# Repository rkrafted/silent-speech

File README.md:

# silent-speech

Research notes and a first-pass hardware design for a personal **silent-speech wearable**: a device that
recognises words articulated without sound from face/jaw/neck biosignals (sEMG), in the spirit of
AlterEgo and Gaddy's silent-speech work.

> **Not tested in real life.** Nothing in this repository has been built, assembled, worn or validated on a
> real person or in a real lab. Hardware designs have only passed software checks (KiCad ERC/DRC and
> netlist scripts), and software/ML results come from offline datasets or a single dev machine. Treat
> everything as an untested design/research artefact. It is provided **as is, with no warranty**, and is
> **not a medical device** and not safe for use on people without independent engineering and safety review.

## What is here

| Path | What |
|---|---|
| `hw/` | **Current design, rev 0.7**: KiCad project for the sensor pod (nRF/NINA-B4 BLE, ADS1298 AFE), dock, cartridge and electrode/charger tabs; schematics, PCB, BOM, netlists, gerbers + pick-and-place in `hw/fab/`, `hw/SPEC.md` and `hw/pod/design-notes.md` |
| `hw/revisions/` | Earlier snapshots of the same design (schematic, PCB, BOM, notes, gerbers where they existed), named `<date>-<hash>` |
| `research/` | 12 general research tracks (SOTA, modalities, electronics, electrodes, ML pipeline, implants, DIY prior art, ear region, e-tattoos, data, Neuralink, fast personalisation) |
| `research/jaw/` | Focused sweeps: patents, PubMed, OpenBCI forum, BLE link, LCSC parts, tantalum, chip forums, articulation design |
| `scripts/`, `tools/` | Small helper scripts used by the research sweeps |
| `docs/` | Notes from one of the research tracks |

Revision snapshots:
- `hw/revisions/2026-10-07-0d3cfc9e/`
- `hw/revisions/2026-10-07-16618296/`
- `hw/revisions/2026-10-07-392cefe4/`
- `hw/revisions/2026-10-07-7efeed88/`
- `hw/revisions/2026-10-16-01f62380/`
- `hw/revisions/2026-10-16-676691bc/`
- `hw/revisions/2026-10-19-591862ab/`

## 3D models

There are **no custom 3D/CAD models** (no STEP/STL for an enclosure) in this repository: the boards reference
KiCad's stock 3D library only, and the NINA-B4 3D model referenced by the footprint was never generated.
Enclosure design has not been started.

## Notes

- Research files cite sources inline; claims marked "unverified" were not confirmed.
- Third-party datasheets, papers and scraped pages are deliberately **not** included.
- Absolute `/home/...` paths remain in some generated KiCad/router files.

## Licence

Software, scripts and documentation: MIT (`LICENSE`). Hardware design files under `hw/`:
CERN-OHL-P-2.0 (`hw/LICENSE-HARDWARE.txt`).

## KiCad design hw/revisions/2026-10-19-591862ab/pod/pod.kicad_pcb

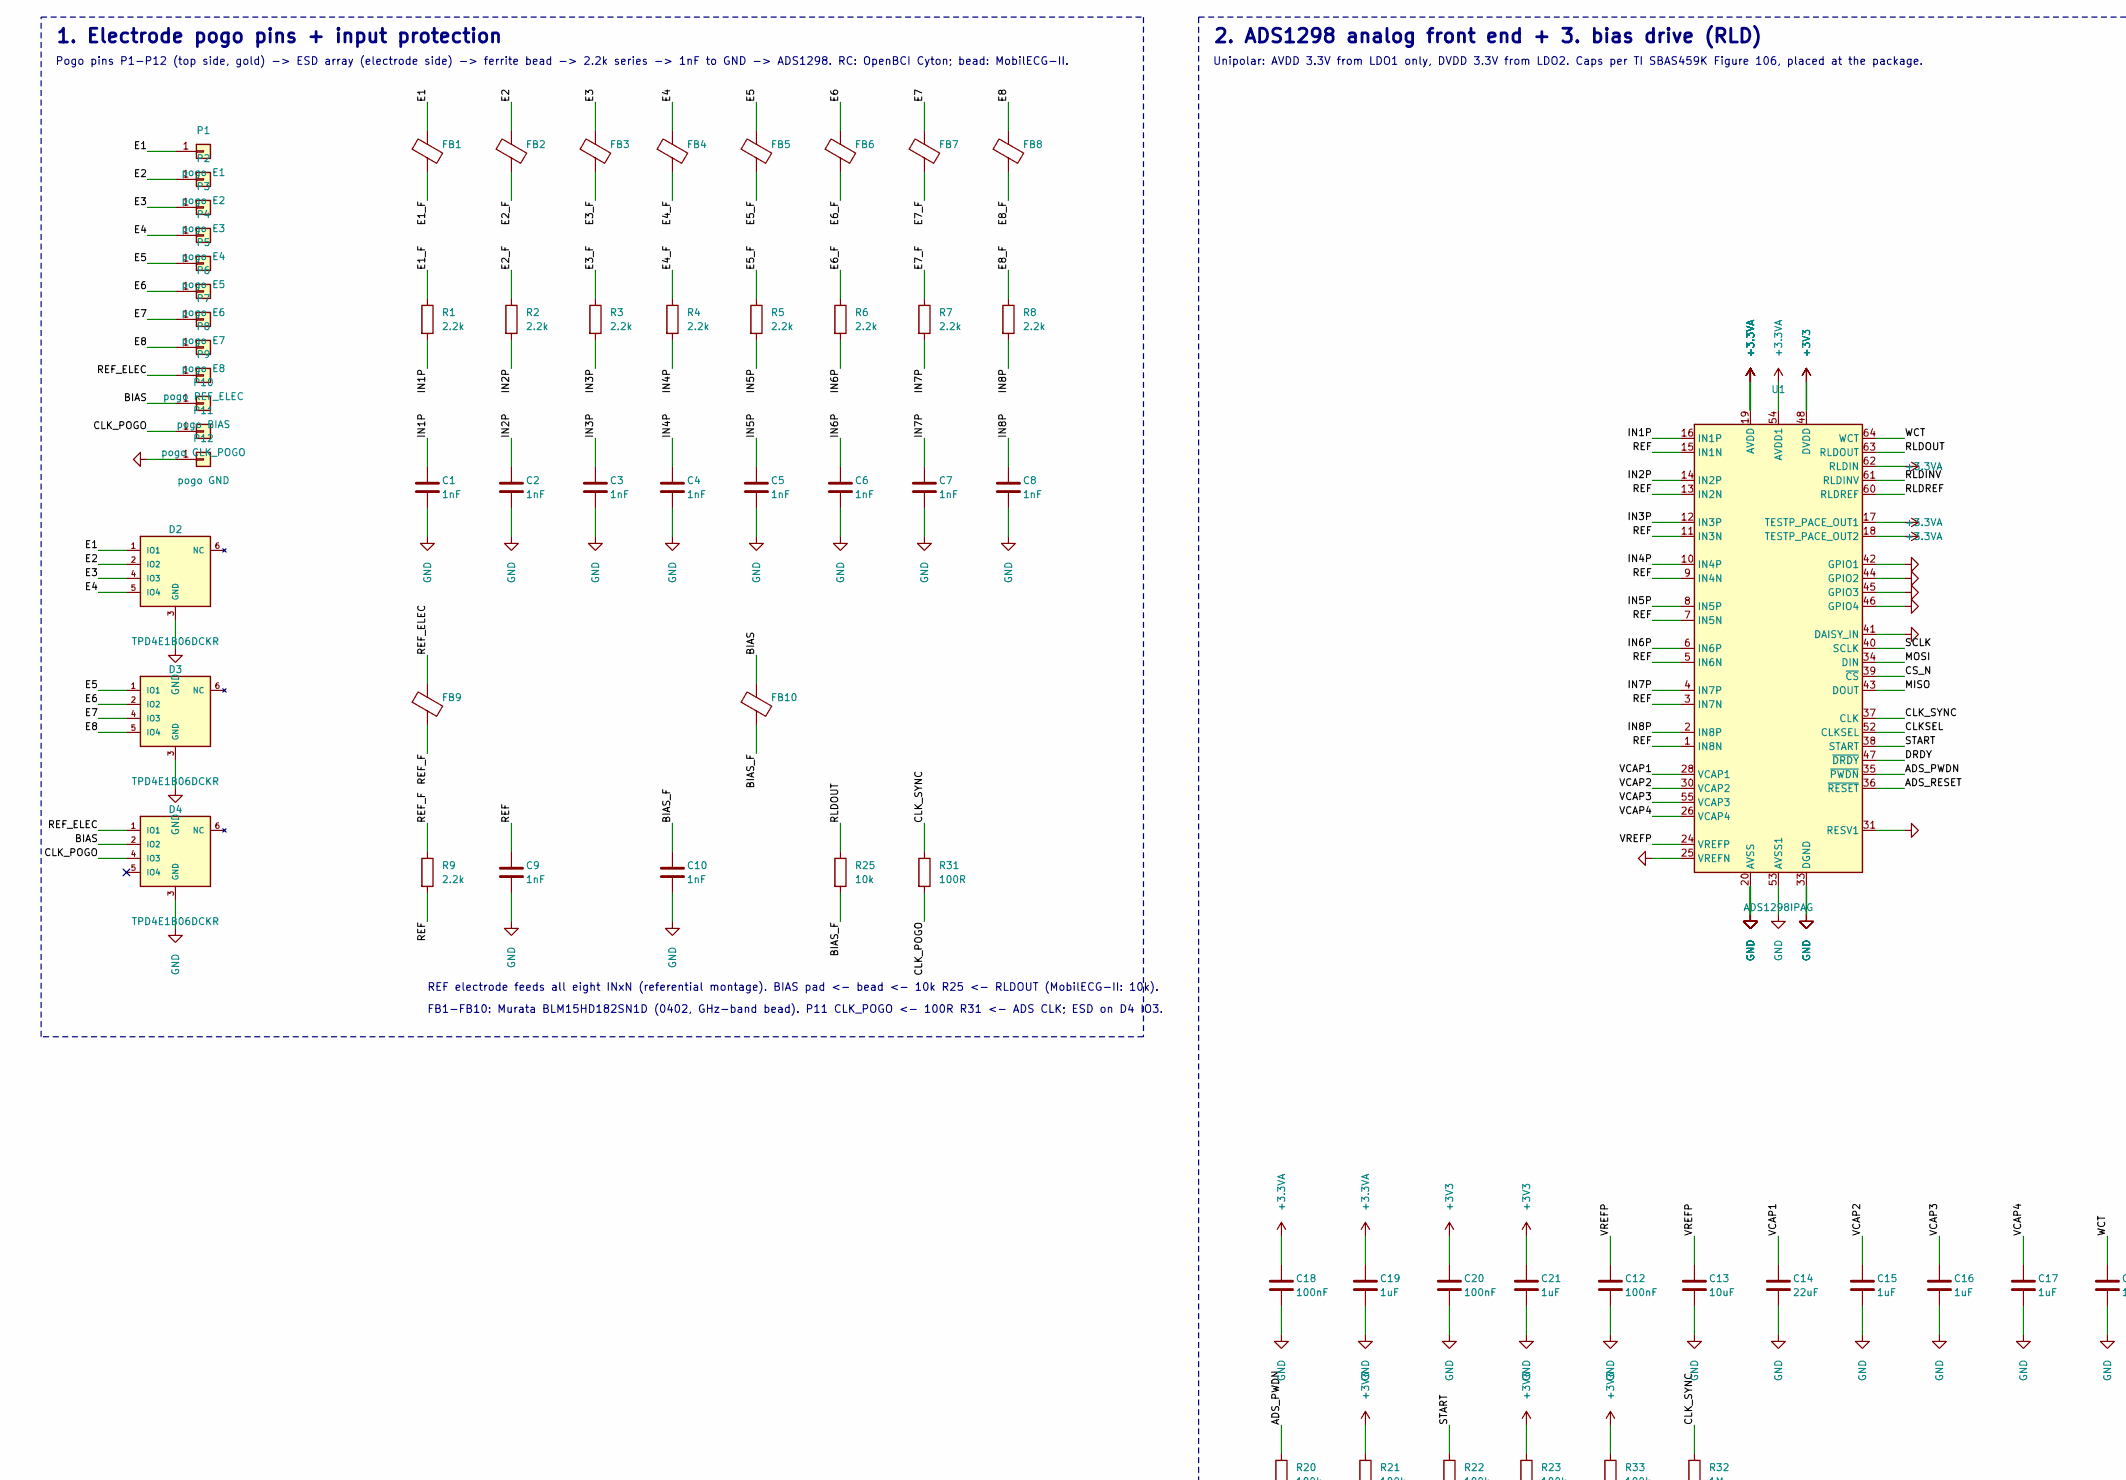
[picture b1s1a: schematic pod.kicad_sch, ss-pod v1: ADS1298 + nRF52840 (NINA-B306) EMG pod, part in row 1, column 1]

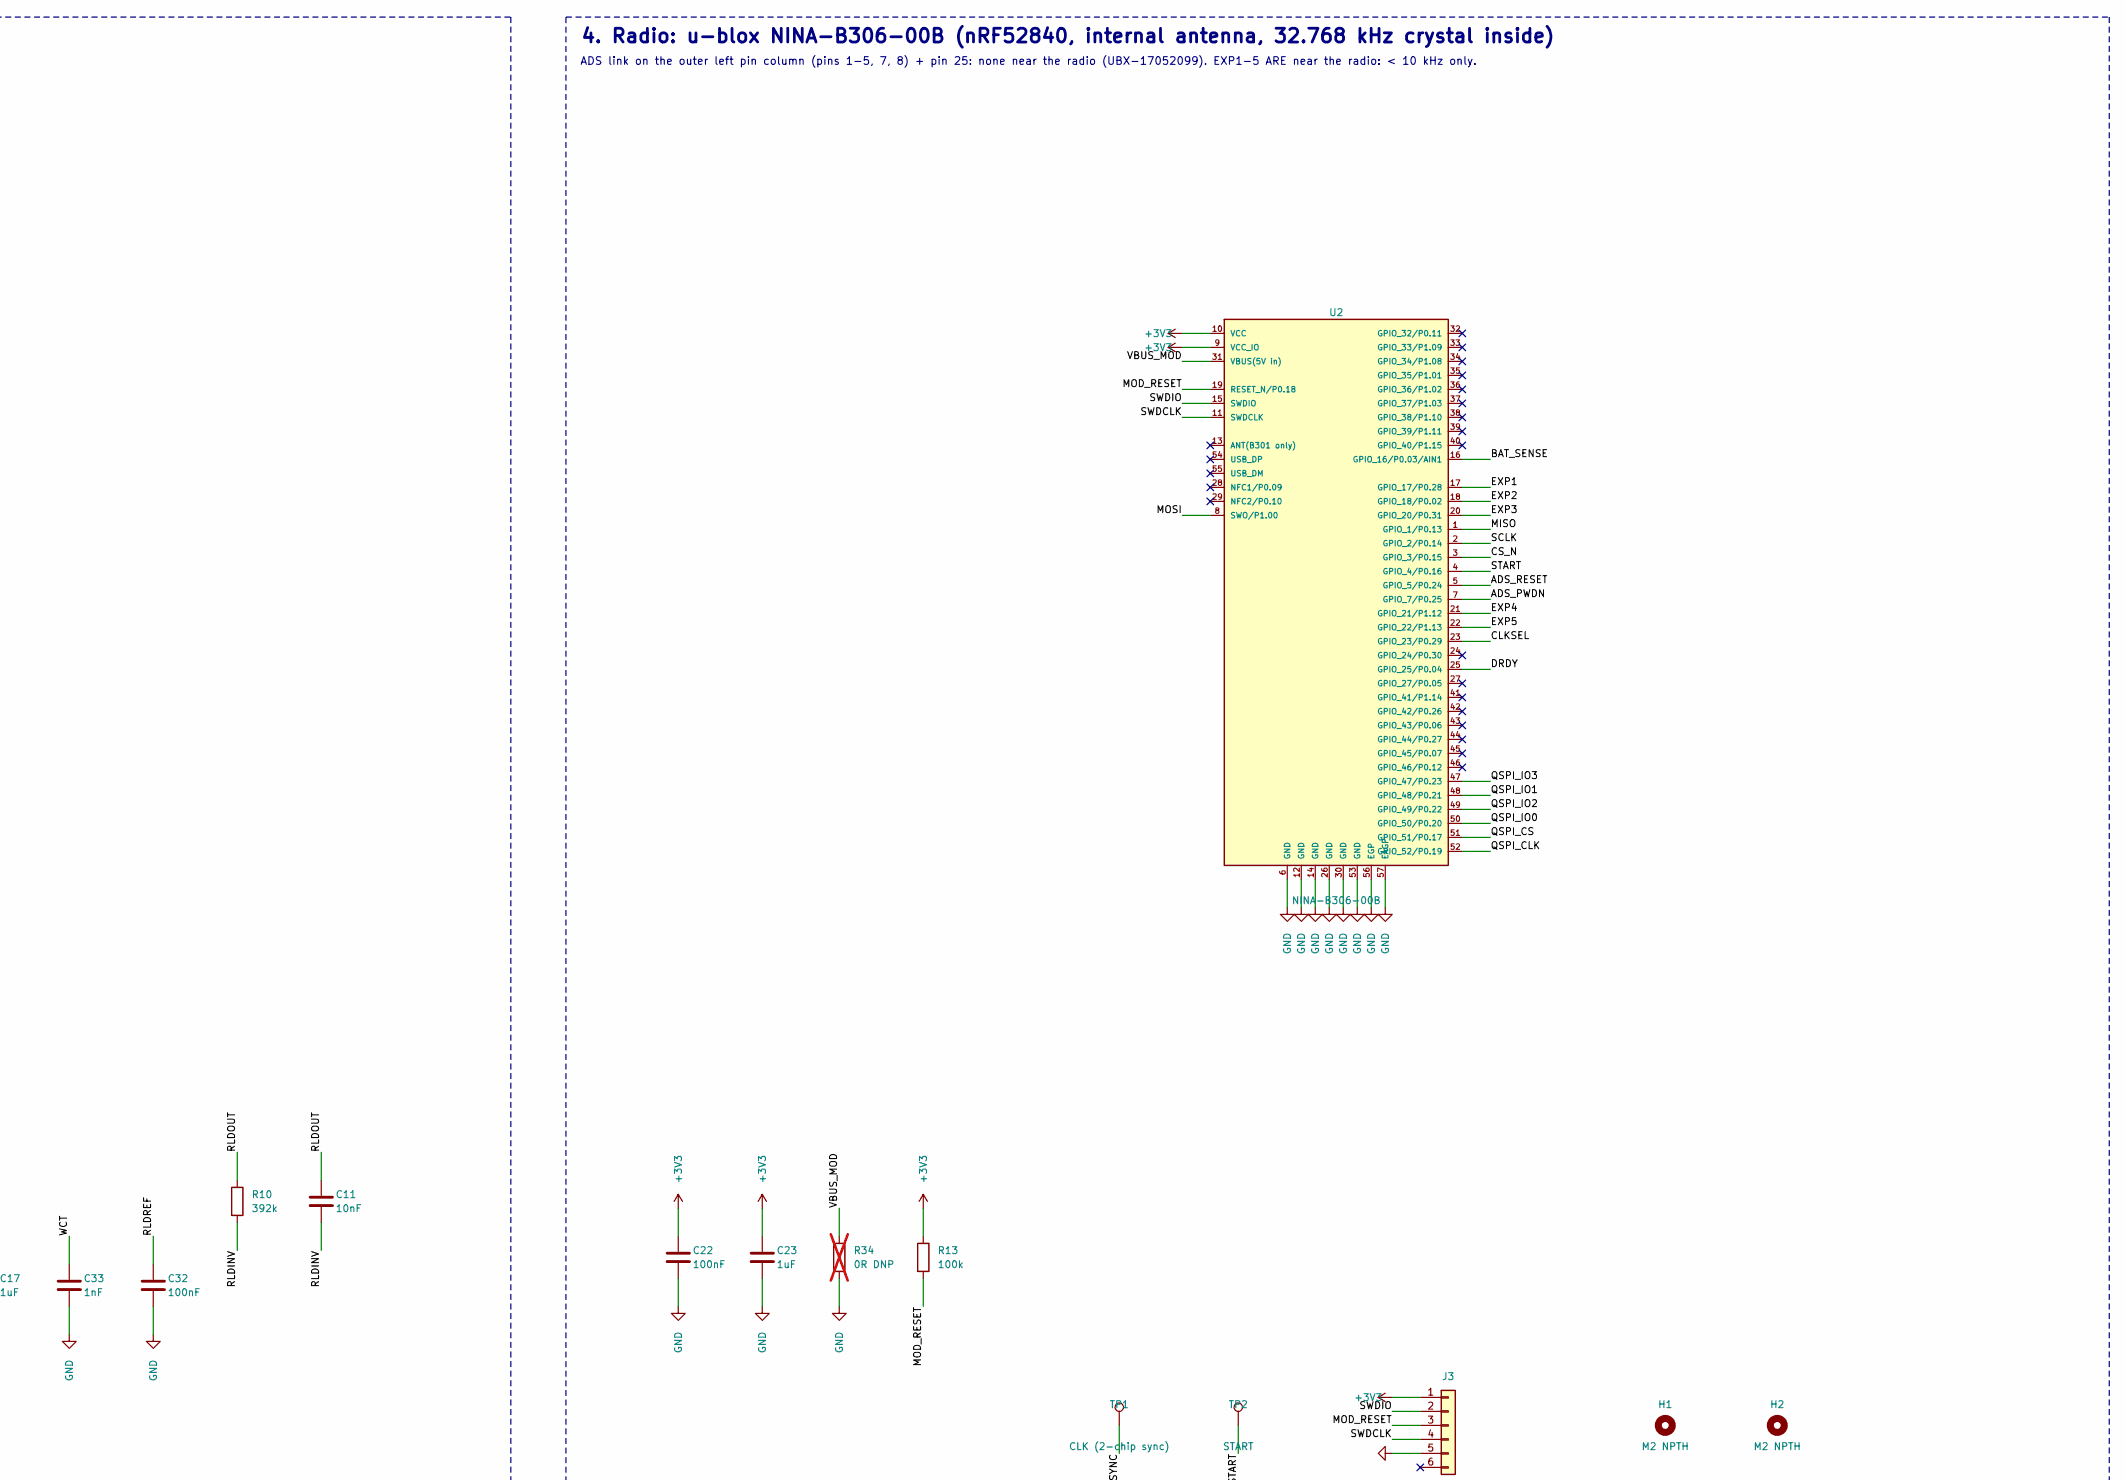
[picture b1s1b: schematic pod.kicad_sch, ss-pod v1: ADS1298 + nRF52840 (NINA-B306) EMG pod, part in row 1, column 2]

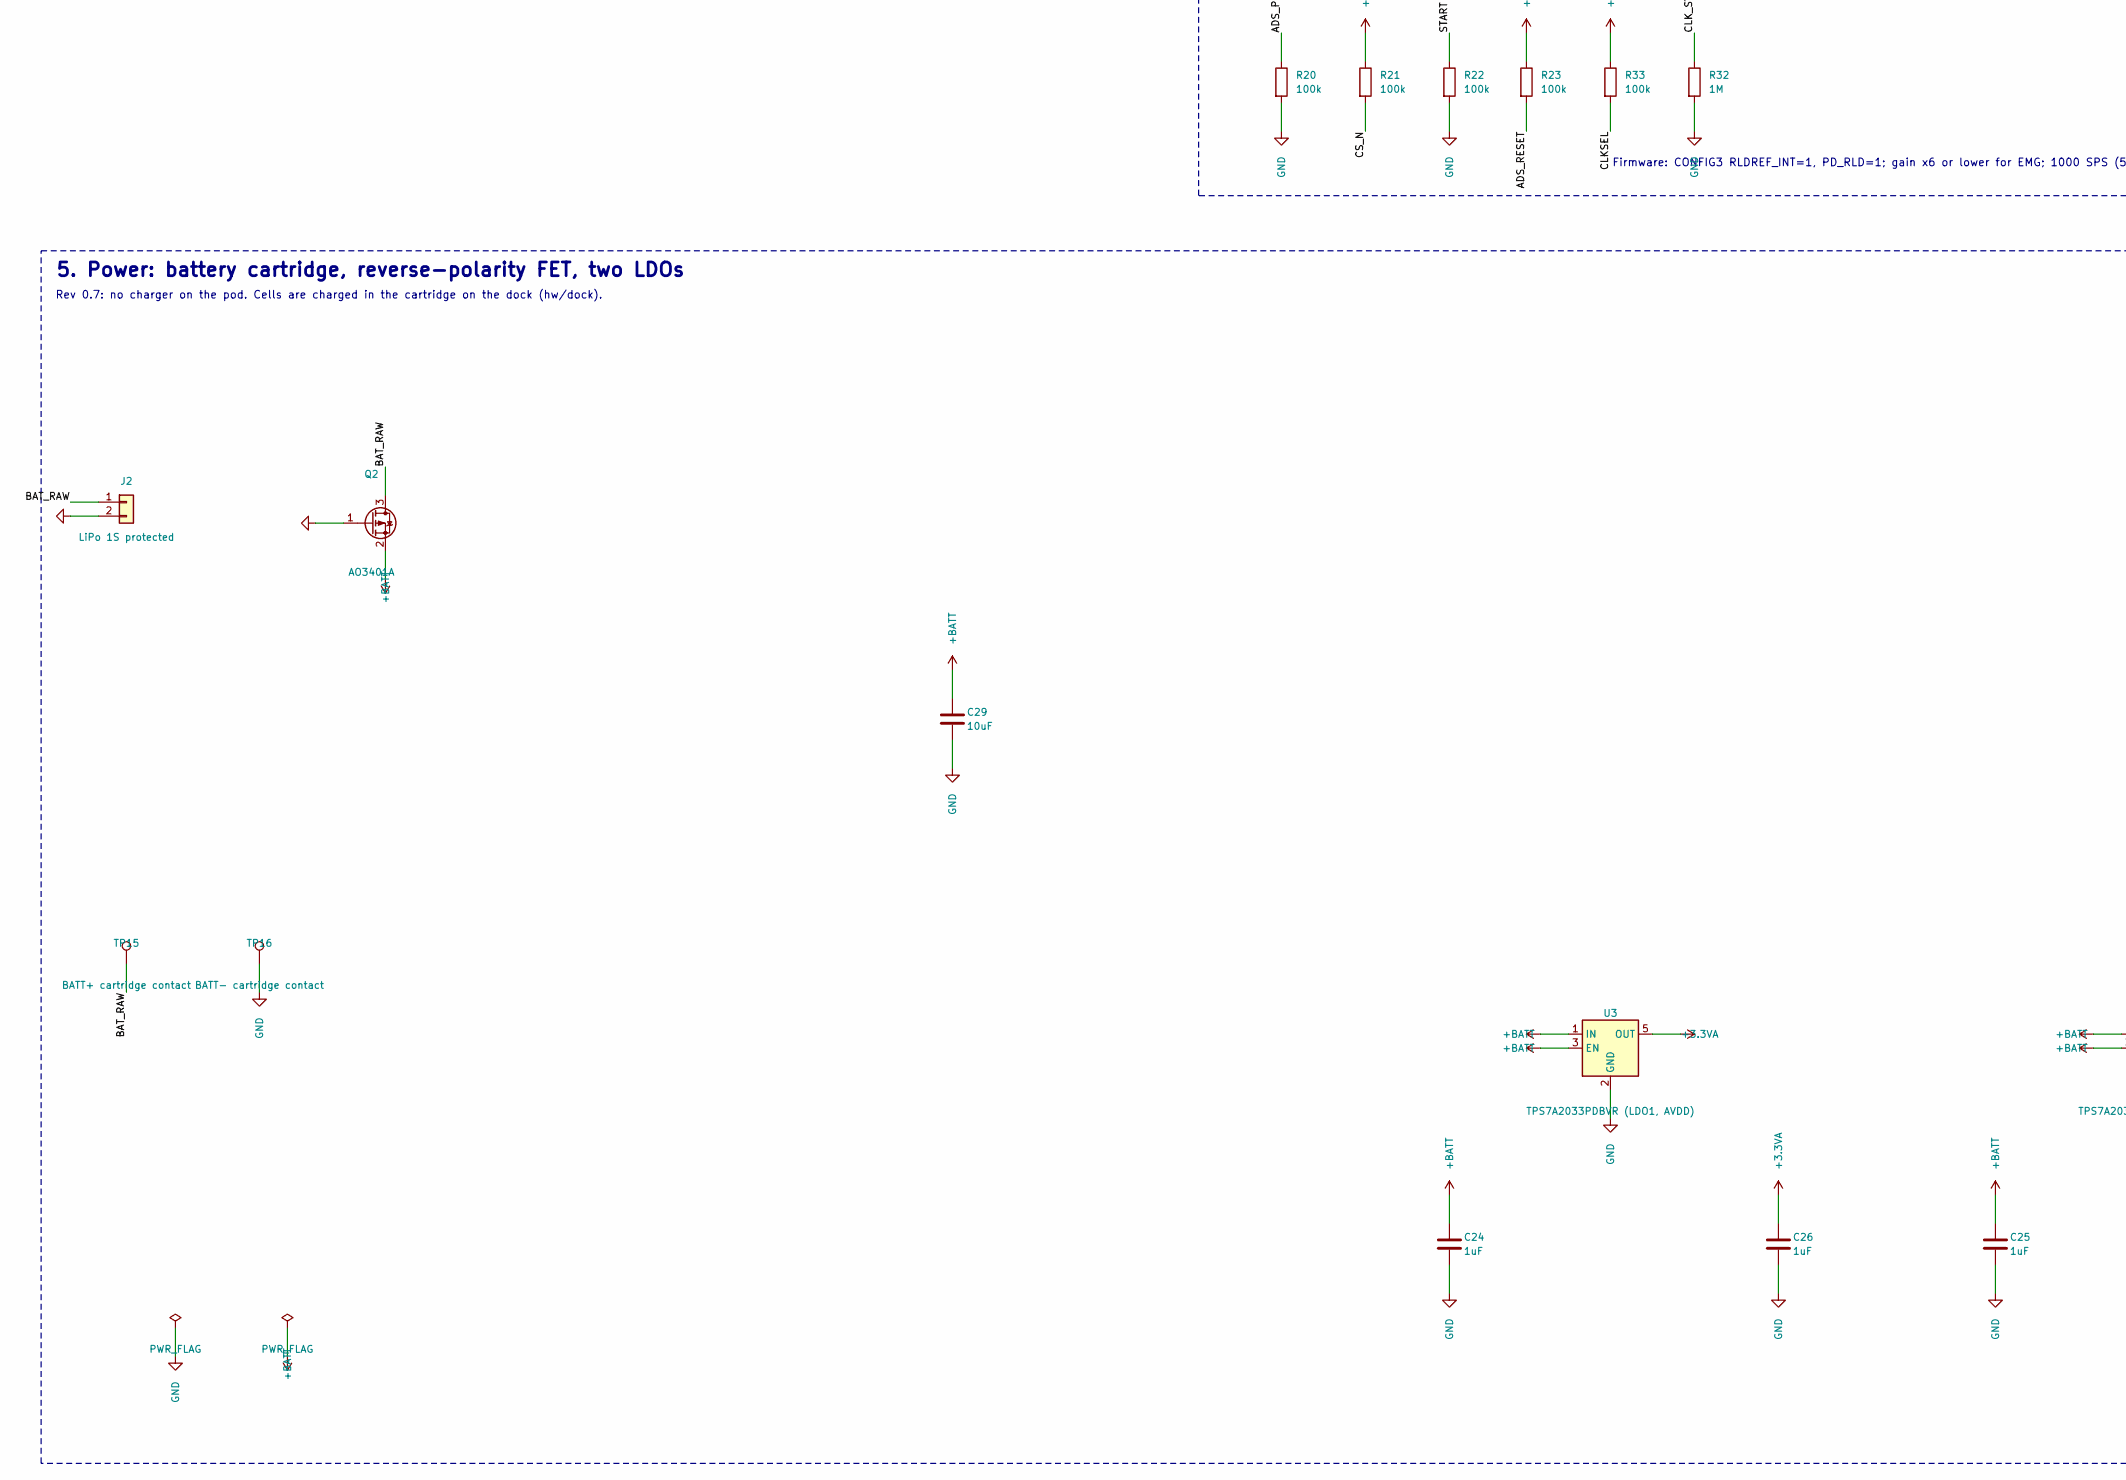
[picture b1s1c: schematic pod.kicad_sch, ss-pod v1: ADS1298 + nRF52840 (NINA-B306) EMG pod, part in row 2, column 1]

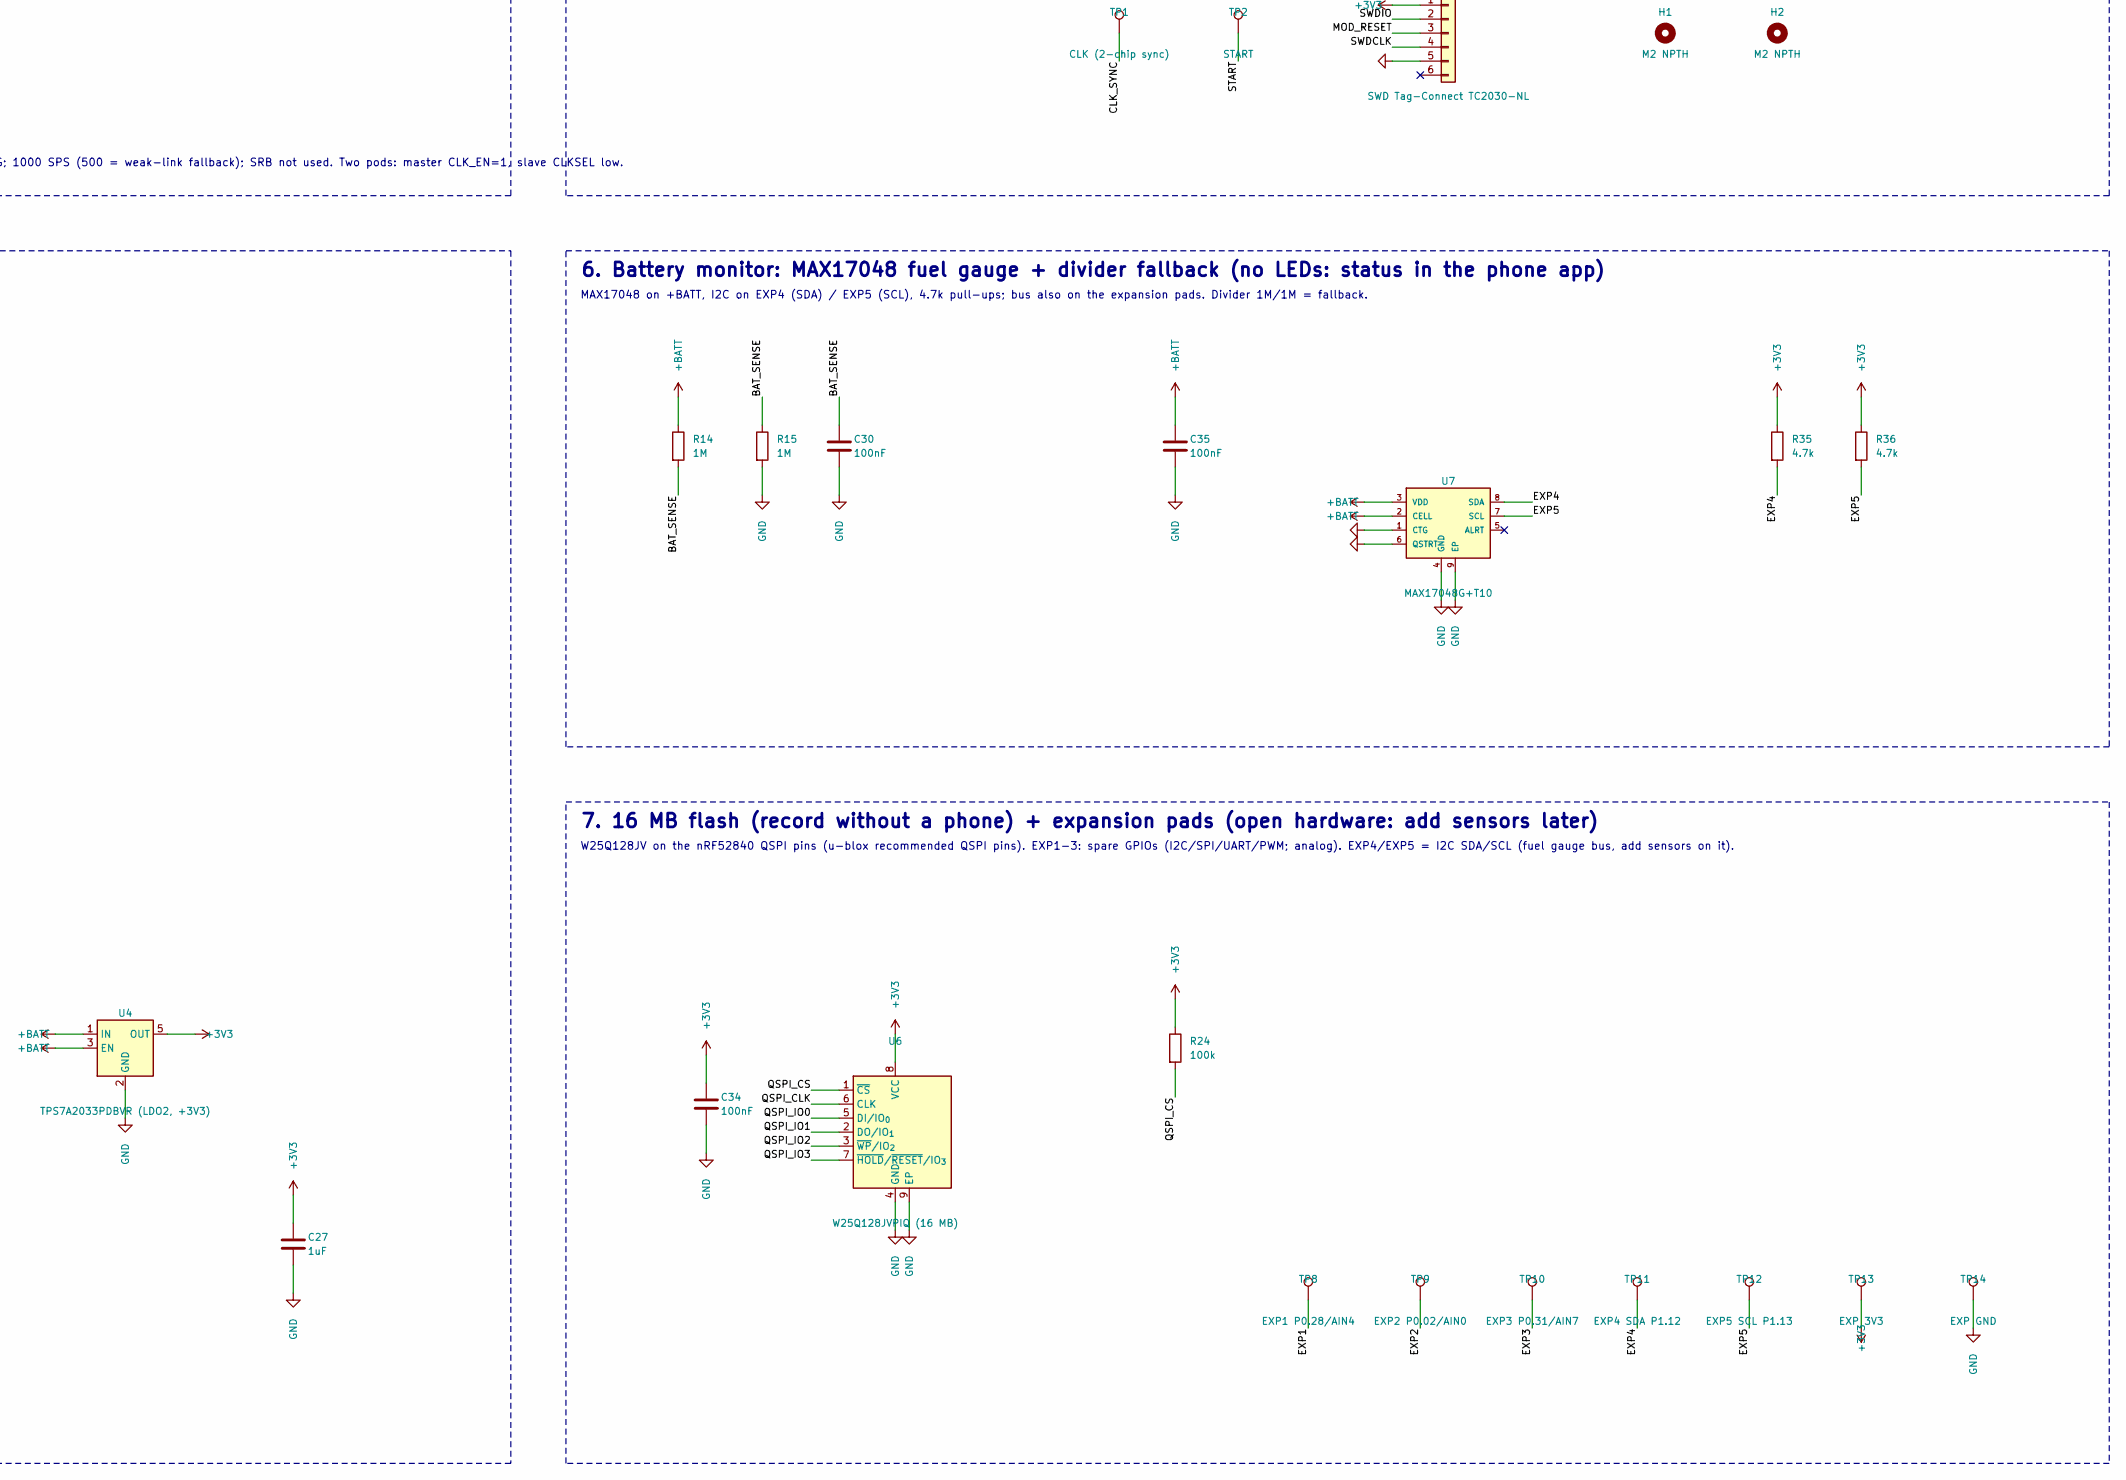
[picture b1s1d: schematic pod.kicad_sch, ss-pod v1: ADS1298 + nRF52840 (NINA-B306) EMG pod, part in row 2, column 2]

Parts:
C1, C2, C3, C4, C5, C6, C7, C8, C9, C10, C33: 1nF; C_0402_1005Metric
C11: 10nF; C_0402_1005Metric
C12, C18, C20, C22, C30, C32, C34, C35: 100nF; C_0402_1005Metric
C13, C29: 10uF; C_0805_2012Metric
C14: 22uF; C_0805_2012Metric
C15, C16, C17, C19, C21, C23, C24, C25, C26, C27: 1uF; C_0402_1005Metric
D2, D3, D4: TPD4E1B06DCKR; SOT-363_SC-70-6
FB1, FB2, FB3, FB4, FB5, FB6, FB7, FB8, FB9, FB10: BLM15HD182SN1D; L_0402_1005Metric
H1, H2: M2 NPTH; M2_NPTH_clamp
J2: LiPo 1S protected; JST_SH_SM02B-SRSS-TB_1x02-1MP_P1.00mm_Horizontal
J3: SWD Tag-Connect TC2030-NL; Tag-Connect_TC2030-IDC-NL_2x03_P1.27mm_Vertical
P1: pogo E1; Harwin_P70-1000045R_pad2.2
P2: pogo E2; Harwin_P70-1000045R_pad2.2
P3: pogo E3; Harwin_P70-1000045R_pad2.2
P4: pogo E4; Harwin_P70-1000045R_pad2.2
P5: pogo E5; Harwin_P70-1000045R_pad2.2
P6: pogo E6; Harwin_P70-1000045R_pad2.2
P7: pogo E7; Harwin_P70-1000045R_pad2.2
P8: pogo E8; Harwin_P70-1000045R_pad2.2
P9: pogo REF_ELEC; Harwin_P70-1000045R_pad2.2
P10: pogo BIAS; Harwin_P70-1000045R_pad2.2
P11: pogo CLK_POGO; Harwin_P70-1000045R_pad2.2
P12: pogo GND; Harwin_P70-1000045R_pad2.2
Q2: AO3401A; SOT-23
R1, R2, R3, R4, R5, R6, R7, R8, R9: 2.2k; R_0402_1005Metric
R10: 392k; R_0402_1005Metric
R13, R20, R21, R22, R23, R24, R33: 100k; R_0402_1005Metric
R14, R15, R32: 1M; R_0402_1005Metric
R25: 10k; R_0402_1005Metric
R31: 100R; R_0402_1005Metric
R34: 0R DNP; R_0402_1005Metric; not fitted
R35, R36: 4.7k; R_0402_1005Metric
TP1: CLK (2-chip sync); TestPad_D0.8mm
TP2: START; TestPad_D0.8mm
TP8: EXP1 P0.28/AIN4; TestPad_D0.8mm
TP9: EXP2 P0.02/AIN0; TestPad_D0.8mm
TP10: EXP3 P0.31/AIN7; TestPad_D0.8mm
TP11: EXP4 SDA P1.12; TestPad_D0.8mm
TP12: EXP5 SCL P1.13; TestPad_D0.8mm
TP13: EXP 3V3; TestPad_D0.8mm
TP14: EXP GND; TestPad_D0.8mm
TP15: BATT+ cartridge contact; TabPad_D1.8mm
TP16: BATT- cartridge contact; TabPad_D1.8mm
U1: ADS1298IPAG; TQFP-64_10x10mm_P0.5mm
U2: NINA-B306-00B; u-blox_NINA-B306
U3: TPS7A2033PDBVR (LDO1, AVDD); SOT-23-5
U4: TPS7A2033PDBVR (LDO2, +3V3); SOT-23-5
U6: W25Q128JVPIQ (16 MB); WSON-8-1EP_6x5mm_P1.27mm_EP3.4x4.3mm
U7: MAX17048G+T10; TDFN-8-1EP_2x2mm_P0.5mm_EP0.8x1.2mm

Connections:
+3.3VA: C18.1, C19.1, C26.1, U1.17 (TESTP_PACE_OUT1), U1.18 (TESTP_PACE_OUT2), U1.19 (AVDD), U1.21 (AVDD), U1.22 (AVDD), U1.54 (AVDD1), U1.56 (AVDD), U1.59 (AVDD), U1.62 (RLDIN), U3.5 (OUT)
+3V3: C20.1, C21.1, C22.1, C23.1, C27.1, C34.1, J3.1, R13.1, R21.1, R23.1, R24.1, R33.1, R35.1, R36.1, TP13.1, U1.48 (DVDD), U1.50 (DVDD), U2.9 (VCC_IO), U2.10 (VCC), U4.5 (OUT), U6.8 (VCC)
+BATT: C24.1, C25.1, C29.1, C35.1, Q2.2 (S), R14.1, U3.1 (IN), U3.3 (EN), U4.1 (IN), U4.3 (EN), U7.2 (CELL), U7.3 (VDD)
/ADS_PWDN: R20.1, U1.35 (~PWDN), U2.7 (GPIO_7/P0.25)
/ADS_RESET: R23.2, U1.36 (~RESET), U2.5 (GPIO_5/P0.24)
/BAT_RAW: J2.1, Q2.3 (D), TP15.1
/BAT_SENSE: C30.1, R14.2, R15.1, U2.16 (GPIO_16/P0.03/AIN1)
/BIAS: D4.2 (IO2), FB10.1, P10.1
/BIAS_F: C10.1, FB10.2, R25.2
/CLKSEL: R33.2, U1.52 (CLKSEL), U2.23 (GPIO_23/P0.29)
/CLK_POGO: D4.4 (IO3), P11.1, R31.2
/CLK_SYNC: R31.1, R32.1, TP1.1, U1.37 (CLK)
/CS_N: R21.2, U1.39 (~CS), U2.3 (GPIO_3/P0.15)
/DRDY: U1.47 (~DRDY), U2.25 (GPIO_25/P0.04)
/E1: D2.1 (IO1), FB1.1, P1.1
/E1_F: FB1.2, R1.1
/E2: D2.2 (IO2), FB2.1, P2.1
/E2_F: FB2.2, R2.1
/E3: D2.4 (IO3), FB3.1, P3.1
/E3_F: FB3.2, R3.1
/E4: D2.5 (IO4), FB4.1, P4.1
/E4_F: FB4.2, R4.1
/E5: D3.1 (IO1), FB5.1, P5.1
/E5_F: FB5.2, R5.1
/E6: D3.2 (IO2), FB6.1, P6.1
/E6_F: FB6.2, R6.1
/E7: D3.4 (IO3), FB7.1, P7.1
/E7_F: FB7.2, R7.1
/E8: D3.5 (IO4), FB8.1, P8.1
/E8_F: FB8.2, R8.1
/EXP1: TP8.1, U2.17 (GPIO_17/P0.28)
/EXP2: TP9.1, U2.18 (GPIO_18/P0.02)
/EXP3: TP10.1, U2.20 (GPIO_20/P0.31)
/EXP4: R35.2, TP11.1, U2.21 (GPIO_21/P1.12), U7.8 (SDA)
/EXP5: R36.2, TP12.1, U2.22 (GPIO_22/P1.13), U7.7 (SCL)
/IN1P: C1.1, R1.2, U1.16 (IN1P)
/IN2P: C2.1, R2.2, U1.14 (IN2P)
/IN3P: C3.1, R3.2, U1.12 (IN3P)
/IN4P: C4.1, R4.2, U1.10 (IN4P)
/IN5P: C5.1, R5.2, U1.8 (IN5P)
/IN6P: C6.1, R6.2, U1.6 (IN6P)
/IN7P: C7.1, R7.2, U1.4 (IN7P)
/IN8P: C8.1, R8.2, U1.2 (IN8P)
/MISO: U1.43 (DOUT), U2.1 (GPIO_1/P0.13)
/MOD_RESET: J3.3, R13.2, U2.19 (RESET_N/P0.18)
/MOSI: U1.34 (DIN), U2.8 (SWO/P1.00)
/QSPI_CLK: U2.52 (GPIO_52/P0.19), U6.6 (CLK)
/QSPI_CS: R24.2, U2.51 (GPIO_51/P0.17), U6.1 (~CS)
/QSPI_IO0: U2.50 (GPIO_50/P0.20), U6.5 (DI/IO_{0})
/QSPI_IO1: U2.48 (GPIO_48/P0.21), U6.2 (DO/IO_{1})
/QSPI_IO2: U2.49 (GPIO_49/P0.22), U6.3 (~WP/IO_{2})
/QSPI_IO3: U2.47 (GPIO_47/P0.23), U6.7 (~HOLD/~RESET/IO_{3})
/REF: C9.1, R9.2, U1.1 (IN8N), U1.3 (IN7N), U1.5 (IN6N), U1.7 (IN5N), U1.9 (IN4N), U1.11 (IN3N), U1.13 (IN2N), U1.15 (IN1N)
/REF_ELEC: D4.1 (IO1), FB9.1, P9.1
/REF_F: FB9.2, R9.1
/RLDINV: C11.2, R10.2, U1.61 (RLDINV)
/RLDOUT: C11.1, R10.1, R25.1, U1.63 (RLDOUT)
/RLDREF: C32.1, U1.60 (RLDREF)
/SCLK: U1.40 (SCLK), U2.2 (GPIO_2/P0.14)
/START: R22.1, TP2.1, U1.38 (START), U2.4 (GPIO_4/P0.16)
/SWDCLK: J3.4, U2.11 (SWDCLK)
/SWDIO: J3.2, U2.15 (SWDIO)
/VBUS_MOD: R34.1, U2.31 (VBUS(5V in))
/VCAP1: C14.1, U1.28 (VCAP1)
/VCAP2: C15.1, U1.30 (VCAP2)
/VCAP3: C16.1, U1.55 (VCAP3)
/VCAP4: C17.1, U1.26 (VCAP4)
/VREFP: C12.1, C13.1, U1.24 (VREFP)
/WCT: C33.1, U1.64 (WCT)
GND: C1.2, C2.2, C3.2, C4.2, C5.2, C6.2, C7.2, C8.2, C9.2, C10.2, C12.2, C13.2, C14.2, C15.2, C16.2, C17.2, C18.2, C19.2, C20.2, C21.2, C22.2, C23.2, C24.2, C25.2, C26.2, C27.2, C29.2, C30.2, C32.2, C33.2, C34.2, C35.2, D2.3 (GND), D3.3 (GND), D4.3 (GND), J2.2, J3.5, P12.1, Q2.1 (G), R15.2, R20.2, R22.2, R32.2, R34.2, TP14.1, TP16.1, U1.20 (AVSS), U1.23 (AVSS), U1.25 (VREFN), U1.31 (RESV1), U1.32 (AVSS), U1.33 (DGND), U1.41 (DAISY_IN), U1.42 (GPIO1), U1.44 (GPIO2), U1.45 (GPIO3), U1.46 (GPIO4), U1.49 (DGND), U1.51 (DGND), U1.53 (AVSS1), U1.57 (AVSS), U1.58 (AVSS), U2.6 (GND), U2.12 (GND), U2.14 (GND), U2.26 (GND), U2.30 (GND), U2.53 (GND), U2.56 (EGP), U2.57 (EAGP), U3.2 (GND), U4.2 (GND), U6.4 (GND), U6.9 (EP), U7.1 (CTG), U7.4 (GND), U7.6 (QSTRT), U7.9 (EP)

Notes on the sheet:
1. Electrode pogo pins + input protection
Pogo pins P1-P12 (top side, gold) -> ESD array (electrode side) -> ferrite bead -> 2.2k series -> 1nF to GND -> ADS1298. RC: OpenBCI Cyton; bead: MobilECG-II.
REF electrode feeds all eight INxN (referential montage). BIAS pad <- bead <- 10k R25 <- RLDOUT (MobilECG-II: 10k).
FB1-FB10: Murata BLM15HD182SN1D (0402, GHz-band bead). P11 CLK_POGO <- 100R R31 <- ADS CLK; ESD on D4 IO3.
2. ADS1298 analog front end + 3. bias drive (RLD)
Unipolar: AVDD 3.3V from LDO1 only, DVDD 3.3V from LDO2. Caps per TI SBAS459K Figure 106, placed at the package.
Firmware: CONFIG3 RLDREF_INT=1, PD_RLD=1; gain x6 or lower for EMG; 1000 SPS (500 = weak-link fallback); SRB not used. Two pods: master CLK_EN=1, slave CLKSEL low.
4. Radio: u-blox NINA-B306-00B (nRF52840, internal antenna, 32.768 kHz crystal inside)
ADS link on the outer left pin column (pins 1-5, 7, 8) + pin 25: none near the radio (UBX-17052099). EXP1-5 ARE near the radio: < 10 kHz only.
5. Power: battery cartridge, reverse-polarity FET, two LDOs
Rev 0.7: no charger on the pod. Cells are charged in the cartridge on the dock (hw/dock).
6. Battery monitor: MAX17048 fuel gauge + divider fallback (no LEDs: status in the phone app)
MAX17048 on +BATT, I2C on EXP4 (SDA) / EXP5 (SCL), 4.7k pull-ups; bus also on the expansion pads. Divider 1M/1M = fallback.
7. 16 MB flash (record without a phone) + expansion pads (open hardware: add sensors later)
W25Q128JV on the nRF52840 QSPI pins (u-blox recommended QSPI pins). EXP1-3: spare GPIOs (I2C/SPI/UART/PWM; analog). EXP4/EXP5 = I2C SDA/SCL (fuel gauge bus, add sensors on it).

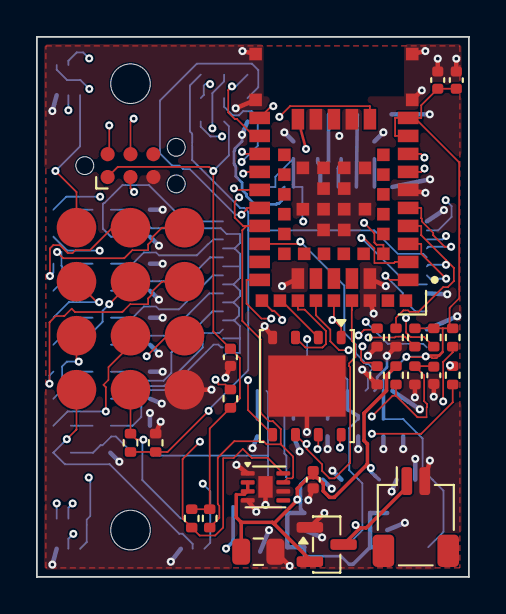
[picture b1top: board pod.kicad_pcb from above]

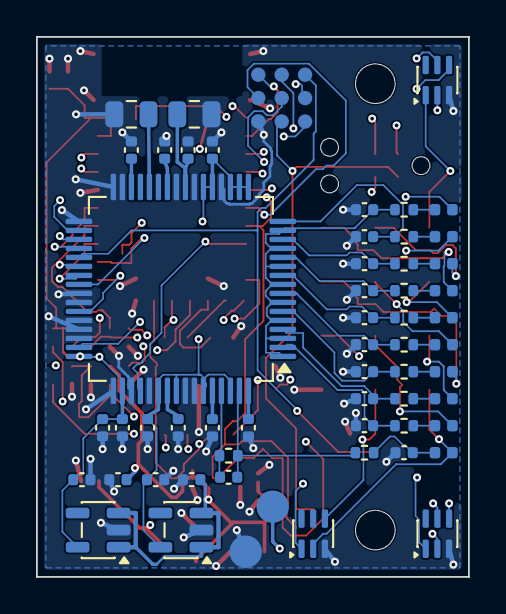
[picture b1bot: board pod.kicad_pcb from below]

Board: 6 copper layers, 24.0 x 30.0 mm, 105 parts (65 on the bottom side), 70 nets.

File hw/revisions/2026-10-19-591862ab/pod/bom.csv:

Reference,Qty,Value,Footprint,MPN,LCSC
"C1,C2,C3,C4,C5,C6,C7,C8,C9,C10,C33",11,"1nF","Capacitor_SMD:C_0402_1005Metric","0402B102K500NT","C1523"
"C11",1,"10nF","Capacitor_SMD:C_0402_1005Metric","CL05B103KB5NNNC","C15195"
"C13,C29",2,"10uF","Capacitor_SMD:C_0805_2012Metric","CL21A106KAYNNNE","C15850"
"C14",1,"22uF","Capacitor_SMD:C_0805_2012Metric","CL21A226MAQNNNE","C45783"
"C18,C20,C12,C32,C22,C35,C30,C34",8,"100nF","Capacitor_SMD:C_0402_1005Metric","CL05B104KO5NNNC","C1525"
"C19,C21,C15,C16,C17,C23,C24,C26,C25,C27",10,"1uF","Capacitor_SMD:C_0402_1005Metric","CL05A105KA5NQNC","C52923"
"D2,D3,D4",3,"TPD4E1B06DCKR","Package_TO_SOT_SMD:SOT-363_SC-70-6","TPD4E1B06DCKR","C840093"
"FB1,FB2,FB3,FB4,FB5,FB6,FB7,FB8,FB9,FB10",10,"BLM15HD182SN1D","Inductor_SMD:L_0402_1005Metric","BLM15HD182SN1D","C76888"
"J2",1,"LiPo 1S protected","Connector_JST:JST_SH_SM02B-SRSS-TB_1x02-1MP_P1.00mm_Horizontal","SM02B-SRSS-TB(LF)(SN)","C160402"
"P1,P2,P3,P4,P5,P6,P7,P8,P9,P10,P11,P12",12,"pogo pin","pod:Harwin_P70-1000045R_pad2.2","P70-1000045R","C17702549"
"Q2",1,"AO3401A","Package_TO_SOT_SMD:SOT-23","AO3401A","C15127"
"R1,R2,R3,R4,R5,R6,R7,R8,R9",9,"2.2k","Resistor_SMD:R_0402_1005Metric","0402WGF2201TCE","C25879"
"R10",1,"392k","Resistor_SMD:R_0402_1005Metric","0402WGF3923TCE","C27007"
"R20,R21,R22,R23,R33,R13,R24",7,"100k","Resistor_SMD:R_0402_1005Metric","0402WGF1003TCE","C25741"
"R25",1,"10k","Resistor_SMD:R_0402_1005Metric","0402WGF1002TCE","C25744"
"R31",1,"100R","Resistor_SMD:R_0402_1005Metric","0402WGF1000TCE","C25076"
"R32,R14,R15",3,"1M","Resistor_SMD:R_0402_1005Metric","0402WGF1004TCE","C26083"
"R35,R36",2,"4.7k","Resistor_SMD:R_0402_1005Metric","0402WGF4701TCE","C25900"
"U1",1,"ADS1298IPAG","Package_QFP:TQFP-64_10x10mm_P0.5mm","ADS1298IPAG","GLOBAL"
"U2",1,"NINA-B306-00B","pod:u-blox_NINA-B306","NINA-B306-00B","C6127317"
"U3,U4",2,"TPS7A2033PDBVR","Package_TO_SOT_SMD:SOT-23-5","TPS7A2033PDBVR","C2862740"
"U6",1,"W25Q128JVPIQ","Package_SON:WSON-8-1EP_6x5mm_P1.27mm_EP3.4x4.3mm","W25Q128JVPIQ","C190862"
"U7",1,"MAX17048G+T10","Package_DFN_QFN:TDFN-8-1EP_2x2mm_P0.5mm_EP0.8x1.2mm","MAX17048G+T10","C2682616"

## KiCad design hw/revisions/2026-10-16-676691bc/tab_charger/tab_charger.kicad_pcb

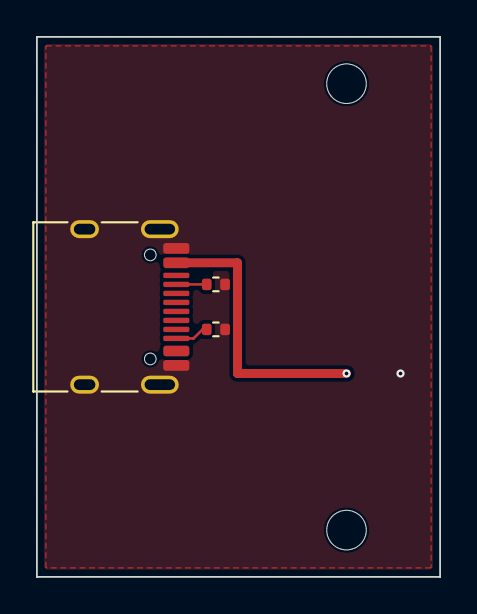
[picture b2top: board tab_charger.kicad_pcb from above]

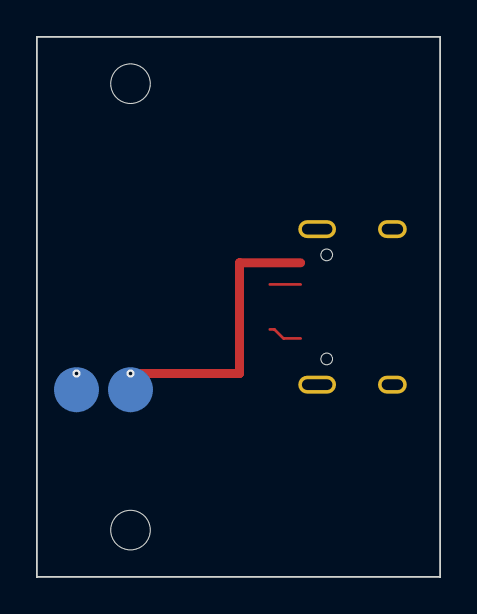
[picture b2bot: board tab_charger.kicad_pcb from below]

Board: 2 copper layers, 22.4 x 30.0 mm, 7 parts (2 on the bottom side), 5 nets.

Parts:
H1, H2: M2_NPTH_clamp
J1: TYPE-C-31-M-12; USB_C_Receptacle_HRO_TYPE-C-31-M-12
P11, P12: TabPad_D2.5mm
R1, R2: 5.1k; R_0402_1005Metric

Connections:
CC1: J1.A5, R1.1
CC2: J1.B5, R2.1
GND: J1.A1, J1.A12, J1.B1, J1.B12, J1.SH, P12.1, R1.2, R2.2
VBUS: J1.A4, J1.B9, P11.1
VBUS_B: J1.A9, J1.B4

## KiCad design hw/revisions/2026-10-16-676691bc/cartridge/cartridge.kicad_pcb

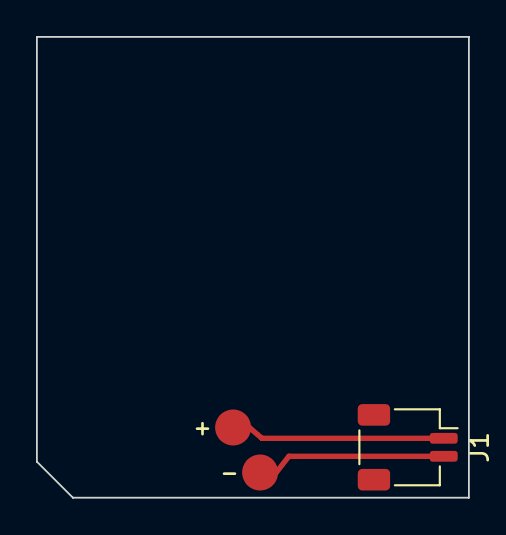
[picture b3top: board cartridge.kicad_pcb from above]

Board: 2 copper layers, 24.0 x 25.6 mm, 3 parts (0 on the bottom side), 2 nets.

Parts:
J1: cell plug (JST SH, pin 1 = +); JST_SH_SM02B-SRSS-TB_1x02-1MP_P1.00mm_Horizontal
P1: pogo 5.5mm BATT+; Pogo_SMD_tall_pad2.0
P2: pogo 5.5mm BATT-; Pogo_SMD_tall_pad2.0

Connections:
BATT+: J1.1, P1.1
BATT-: J1.2, P2.1

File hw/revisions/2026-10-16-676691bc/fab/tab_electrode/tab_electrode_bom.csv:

Comment,Designator,Footprint,LCSC Part #
2x5 2.54mm SMD vertical pin header,J1,PinHeader_2x05_P2.54mm_Vertical_SMD,

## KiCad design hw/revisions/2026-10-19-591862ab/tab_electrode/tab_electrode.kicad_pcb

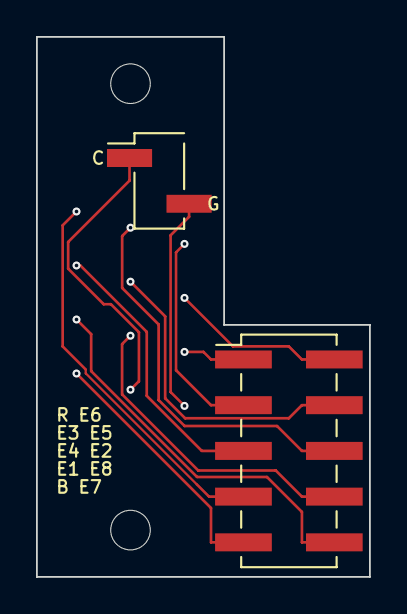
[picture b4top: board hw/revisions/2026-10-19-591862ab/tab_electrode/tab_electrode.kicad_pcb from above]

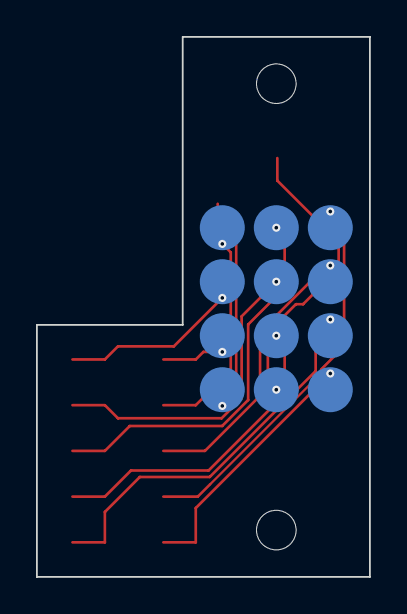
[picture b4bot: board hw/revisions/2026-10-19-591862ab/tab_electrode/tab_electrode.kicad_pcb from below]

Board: 2 copper layers, 18.5 x 30.0 mm, 16 parts (12 on the bottom side), 12 nets.

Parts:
H1, H2: M2_NPTH_clamp
J1: 2x5 2.54 SMD vertical; PinHeader_2x05_P2.54mm_Vertical_SMD
J2: 1x2 2.54 SMD vertical (link); PinHeader_1x02_P2.54mm_Vertical_SMD_Pin1Left
P1, P2, P3, P4, P5, P6, P7, P8, P9, P10, P11, P12: TabPad_D2.5mm

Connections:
BIAS: J1.9, P10.1
CLK: J2.1, P11.1
E1: J1.7, P1.1
E2: J1.6, P2.1
E3: J1.3, P3.1
E4: J1.5, P4.1
E5: J1.4, P5.1
E6: J1.2, P6.1
E7: J1.10, P7.1
E8: J1.8, P8.1
GND: J2.2, P12.1
REF: J1.1, P9.1

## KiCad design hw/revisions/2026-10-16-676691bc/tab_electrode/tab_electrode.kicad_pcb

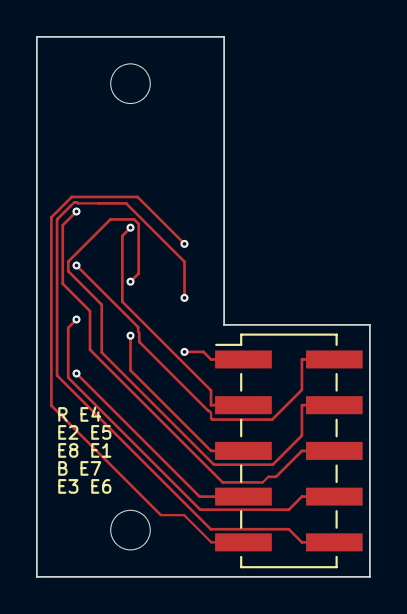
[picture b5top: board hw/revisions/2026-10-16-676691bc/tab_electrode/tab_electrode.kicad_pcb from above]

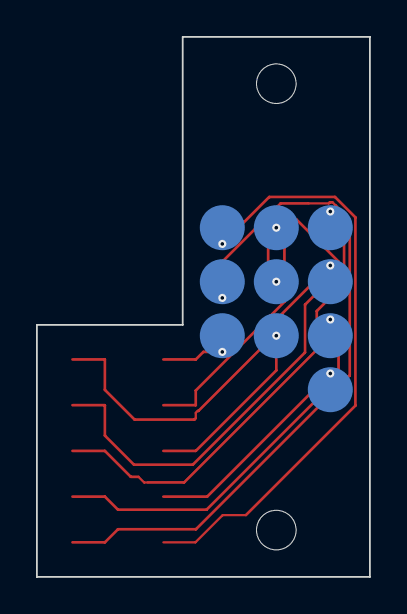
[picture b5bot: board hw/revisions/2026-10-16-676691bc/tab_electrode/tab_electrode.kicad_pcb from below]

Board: 2 copper layers, 18.5 x 30.0 mm, 13 parts (10 on the bottom side), 10 nets.

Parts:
H1, H2: M2_NPTH_clamp
J1: 2x5 2.54 SMD vertical; PinHeader_2x05_P2.54mm_Vertical_SMD
P1, P2, P3, P4, P5, P6, P7, P8, P9, P10: TabPad_D2.5mm

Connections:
BIAS: J1.7, P10.1
E1: J1.6, P1.1
E2: J1.3, P2.1
E3: J1.9, P3.1
E4: J1.2, P4.1
E5: J1.4, P5.1
E6: J1.10, P6.1
E7: J1.8, P7.1
E8: J1.5, P8.1
REF: J1.1, P9.1
